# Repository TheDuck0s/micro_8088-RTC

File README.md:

# Micro 8088 + RTC

This is an IBM XT-compatible CPU and RTC card, based on a design by [Sergey Kiselev](https://github.com/skiselev) and [Aitor Gómez García](https://github.com/spark2k06).

# The Idea

The goal of this project is to create an XT-compatible computer on a passive backplane with a modular card-based architecture, minimizing the overall footprint while providing support for all common expansion cards.

# Hardware Documentation
Schematic PDF:
[Schematic - Version 1.0](Micro_8088-RTC_Schematic.pdf)

PCB PDF:
[Board Design - Version 1.0](Micro_8088-RTC_Board_Design.pdf)

Gerber Files:
[Gerber- Version 1.0](gerber/)

SPLD:

* U16 CPU-Part:
[Use the repository provided by Sergey Kiselev](https://github.com/skiselev/micro_8088/tree/master/SPLD)

* U17 RTC-Part:
[Use the repository provided by Sergey Kiselev](https://github.com/skiselev/RTC8088/tree/main/SPLD)

AT2XT Firmware:
* U15 [minuszerodegrees.net](http://minuszerodegrees.net/at2xtkb/XTATKEY_094.zip)

# Bill of Materials

Component type    	| Reference | Description                       | Quantity 
------------------ | --------- | --------------------------------- | -------- 
PCB                |           | Micro 8080 + RTC PCB              | 1        
Integrated Circuit | U1        | Intel 8088, 80C88, or NEC V20 CPU | 1        
Integrated Circuit | U2        | Intel 8087 FPU                    | 1        
Integrated Circuit | U3        | Faraday FE2010A                   | 1        
Integrated Circuit | U4        | SST39SF010A Flash ROM, DIP-32 package | 1    
Integrated Circuit | U5, U6    | AS6C4008 SRAM, DIP-32 package     | 2        
Integrated Circuit | U7 - U9   | 74F573 Octal D-Type Latch         | 3        
Integrated Circuit | U10, U11  | 74F245 Octal Bus Transceiver      | 2        
Integrated Circuit | U12, U13  | 74F244 Octal Buffer               | 2        
Integrated Circuit | U14       | 74F00 Quad 2-Input NAND Gate      | 1        
Integrated Circuit | U15       | PIC12F629 Microcontroller         | 1        
Integrated Circuit | U16       | ATF16V8B SPLD                     | 1        
IC Socket          | U1, U2    | DIP-40, 600 mil socket            | 2        
IC Socket          | U3        | PLCC-84 through hole socket       | 1        
IC Socket          | U4-U6     | DIP-32, 600 mil socket            | 3        
IC Socket          | U7-U13, U16, U17 | DIP-20, 300 mil socket     | 9        
IC Socket          | U14       | DIP-14, 300 mil socket            | 1        
IC Socket          | U15       | DIP-8, 300 mil socket             | 1        
IC Socket          | U18       | DIP-24, 600 mil socket            | 1
Diode              | D1        | 1N4148                            | 1        
LED                | D2        | 3 mm, green LED indicator         | 1        
Transistor         | Q1        | PN2222A, 2.54mm lead spacing      | 1        
Crystal            | X1        | 28.63636 MHz, 18 pF, HC-49/S      | 1        
Crystal            | X2        | 32768Hz                           | 1
Battery            | BT1       | Battery socket                    | 1
Speaker            | SP1       | 12 mm speaker                     | 1        
Tactile Button     | SW1       | 6 mm tactile button, right angle  | 1        
DIP Switch         | SW2, SW3  | 3 positions                       | 2        
DIP Switch         | SW4       | 5 positions                       | 1        
Connector          | P1        | 6 pin Mini DIN, purple            | 1        
Pin Header         | P2        | 4 pin header, 2.54 mm pitch       | 1        
Pin Header         | P3, JP1-JP5 | 2 pin header, 2.54 mm pitch     | 6        
Capacitor          | C1 - C18  | 0.1 uF, MLCC, 5 mm lead spacing   | 19       
Capacitor          | C18 - C20 | 10 uF, MLCC, 5 mm lead spacing    | 3        
Trimmer Capacitor  | C21       | 6.5-30 pF, 5 mm lead spacing      | 1        
Capacitor          | C22       | 47 pF, MLCC, 5 mm lead spacing    | 1        
Capacitor          | C23       | 0.01 uF, MLCC, 5 mm lead spacing  | 1        
Resistor Array     | RR1       | 4.7 k, bussed, 10 pin SIP         | 1        
Resistor Array     | RR2       | 10 k, bussed, 10 pin SIP          | 1        
Resistor Array     | RR3, RR4  | 4.7 k, bussed, 6 pin SIP          | 2        
Resistor Array     | RR5, RR6  | 10 k, bussed, 6 pin SIP           | 2        
Resistor           | R1        | 33 ohm, through hole              | 1        
Resistor           | R2, R3    | 47 ohm, through hole              | 2        
Resistor           | R4, R5    | 470 ohm, through hole             | 2        
Resistor           | R6        | 1 kohm, through hole              | 1        
Resistor           | R7        | 10 kohm, through hole             | 1        
Resistor           | R8        | 1 Mohm, through hole              | 1        
Fuse               | F1        | 1.1A polyfuse, 5.08 mm lead pitch | 1        
ISA Bracket        |           | Keystone Electronics 9202         | 1        
Screw              |           | 4-40 x 1/4" Screw                 | 2        

# Release Notes

### Changes:

#### Version 1.0

 * Initial Release

# Benchmarks
 * CPU: D70108HCZ-16
 * FPU: 8087-1

### Checkit 3.0 Benchmark:
#### @4.77 MHz
 * 414 Dhrystones (1.20x)
 * 126.9K Whetstones (19.23x)

#### @7.16 MHz
 * 618 Dhrystones (1.80x)
 * 191.3K Whetstones (28.97x)

#### @9.55 MHz
 * 837 Dhrystones (2.43x)
 * 267.7K Whetstones (40.56x)

# Final Note
 * Install either U14 or U16, not both together
 * The card is tested and works.
 * This card won't fit Sergey's case ([this one](https://github.com/skiselev/micro_8088_case)). The case will need to be enlarged.
 * Card size 185.3 mm x 102.9 mm

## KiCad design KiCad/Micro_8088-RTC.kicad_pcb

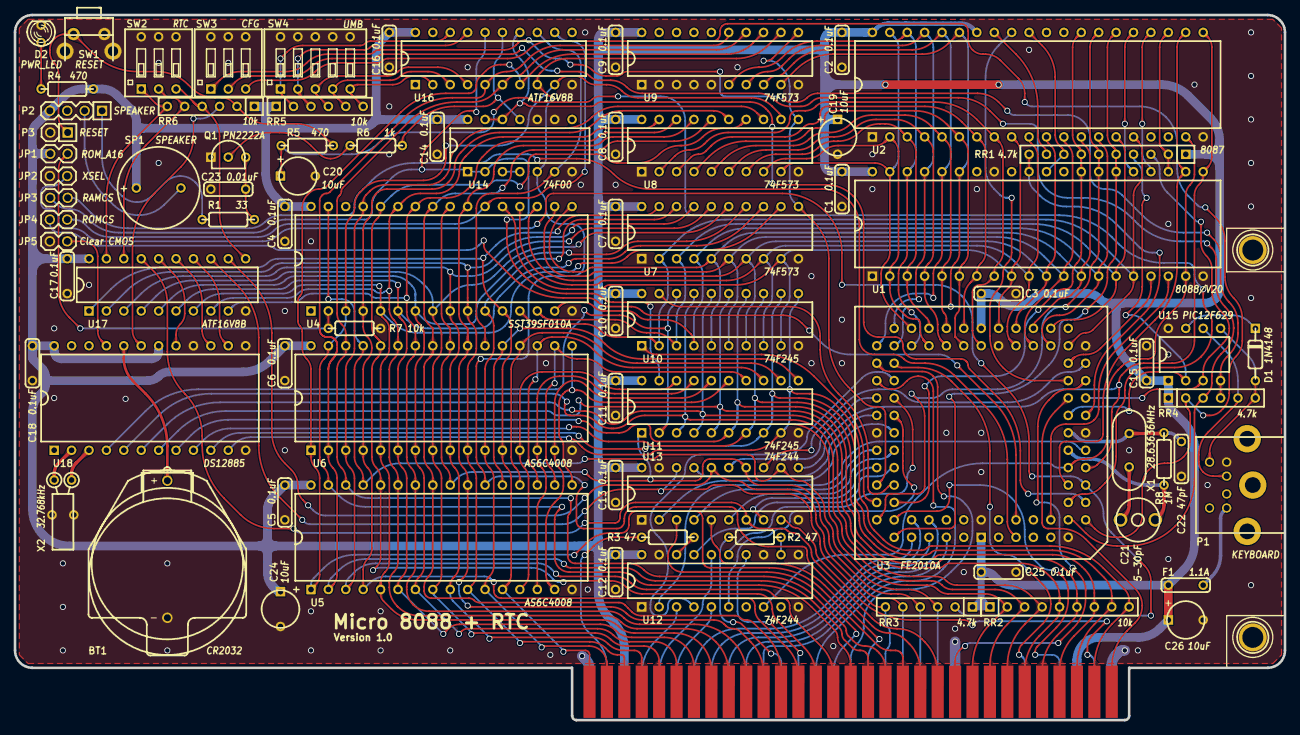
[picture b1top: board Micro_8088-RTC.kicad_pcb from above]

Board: 2 copper layers, 185.3 x 102.9 mm, 81 parts (0 on the bottom side), 160 nets.

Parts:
BT1: CR2032; Battery_Holder_CR2032_Universal
BUS1: BUSPC_HOST; Conn_Edge_PCB_ISA8
C1, C2, C3, C4, C5, C6, C7, C8, C9, C10, C11, C12, C13, C14, C15, C16, C17, C18, C25: 0.1uF; Cap_Cer_508
C19, C20, C24, C26: 10uF; Cap_Tant_508
C21: 5-30pF; C_Trim_Murata
C22: 47pF; Cap_Cer_508
C23: 0.01uF; Cap_Cer_508
D1: 1N4148; Diode_762
D2: PWR_LED; LED_3mm
F1: 1.1A; Cap_Cer_508
HOLE1, HOLE2: HOLE; Hole_3mm
JP1: ROM_A16; Conn_Pin_Header_2x1_2.54mm_NoKey
JP2: XSEL; Conn_Pin_Header_2x1_2.54mm_NoKey
JP3: RAMCS; Conn_Pin_Header_2x1_2.54mm_NoKey
JP4: ROMCS; Conn_Pin_Header_2x1_2.54mm_NoKey
JP5: Clear CMOS; Conn_Pin_Header_2x1_2.54mm_NoKey
P1: KEYBOARD; Conn_Mini_DIN_6pin
P2: SPEAKER; Conn_Pin_Header_4x1_2.54mm
P3: RESET; Conn_Pin_Header_2x1_2.54mm
Q1: PN2222A; Transistor_TO92_EBC_254
R1: 33; Res_762
R2, R3: 47; Res_762
R4, R5: 470; Res_762
R6: 1k; Res_762
R7: 10k; Res_762
R8: 1M; Res_762
RR1: 4.7k; Conn_SIL10
RR2: 10k; Conn_SIL9
RR3, RR4: 4.7k; Conn_SIL6
RR5, RR6: 10k; Conn_SIL6
SP1: SPEAKER; Speaker_12mm
SW1: RESET; Switch_Tactile_6mm_Right
SW2: RTC; Switch_DIP_3_Positions
SW3: CFG; Switch_DIP_3_Positions
SW4: UMB; Switch_DIP_5_Positions
U1: 8088/V20; IC_DIP40_600
U2: 8087; IC_DIP40_600
U3: FE2010A; IC_PLCC84_TH
U4: SST39SF010A; IC_DIP32_600
U5, U6: AS6C4008; IC_DIP32_600
U7, U8, U9: 74F573; IC_DIP20_300
U10, U11: 74F245; IC_DIP20_300
U12, U13: 74F244; IC_DIP20_300
U14: 74F00; IC_DIP14_300
U15: PIC12F629; IC_DIP8_300
U16, U17: ATF16V8B; IC_DIP20_300
U18: DS12885; IC_DIP24_600
X1: 28.63636MHz; Crystal_HC-49U_Vert
X2: 32.768kHz; Crystal_32K_Horiz

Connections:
/A0: BUS1.62 (SA0), U4.12 (A0), U5.12 (A0), U6.12 (A0), U7.19 (O0), U17.1 (I/CLK)
/A1: BUS1.61 (SA1), U4.11 (A1), U5.11 (A1), U6.11 (A1), U7.18 (O1)
/A2: BUS1.60 (SA2), U4.10 (A2), U5.10 (A2), U6.10 (A2), U7.17 (O2), U17.2 (I1)
/A3: BUS1.59 (SA3), U4.9 (A3), U5.9 (A3), U6.9 (A3), U7.16 (O3), U17.3 (I2)
/A4: BUS1.58 (SA4), U4.8 (A4), U5.8 (A4), U6.8 (A4), U7.15 (O4), U17.4 (I3)
/A5: BUS1.57 (SA5), U4.7 (A5), U5.7 (A5), U6.7 (A5), U7.14 (O5), U17.5 (I4)
/A6: BUS1.56 (SA6), U4.6 (A6), U5.6 (A6), U6.6 (A6), U7.13 (O6), U17.6 (I5)
/A7: BUS1.55 (SA7), U4.5 (A7), U5.5 (A7), U6.5 (A7), U7.12 (O7), U17.7 (I6)
/A8: BUS1.54 (SA8), U4.27 (A8), U5.27 (A8), U6.27 (A8), U8.19 (O0), U17.8 (I7)
/A9: BUS1.53 (SA9), U4.26 (A9), U5.26 (A9), U6.26 (A9), U8.18 (O1), U17.9 (I8)
/A10: BUS1.52 (SA10), U4.23 (A10), U5.23 (A10), U6.23 (A10), U8.17 (O2)
/A11: BUS1.51 (SA11), U4.25 (A11), U5.25 (A11), U6.25 (A11), U8.16 (O3)
/A12: BUS1.50 (SA12), U4.4 (A12), U5.4 (A12), U6.4 (A12), U8.15 (O4)
/A13: BUS1.49 (SA13), U4.28 (A13), U5.28 (A13), U6.28 (A13), U8.14 (O5)
/A14: BUS1.48 (SA14), U4.29 (A14), U5.3 (A14), U6.3 (A14), U8.13 (O6)
/A15: BUS1.47 (SA15), U4.3 (A15), U5.31 (A15), U6.31 (A15), U8.12 (O7), U16.9 (I8)
/A16: BUS1.46 (SA16), U5.2 (A16), U6.2 (A16), U9.15 (O4), U16.5 (I4)
/A17: BUS1.45 (SA17), U5.30 (A17), U6.30 (A17), U9.14 (O5), U16.6 (I5)
/A18: BUS1.44 (SA18), U5.1 (A18), U6.1 (A18), U9.13 (O6), U16.7 (I6)
/A19: BUS1.43 (SA19), U5.22 (~CE), U9.12 (O7), U14.5, U16.8 (I7)
/AA8: U1.8 (A8), U2.8 (AD8), U3.44 (A8), U8.2 (D0)
/AA9: U1.7 (A9), U2.7 (AD9), U3.45 (A9), U8.3 (D1)
/AA10: U1.6 (A10), U2.6 (AD10), U3.46 (A10), U8.4 (D2)
/AA11: U1.5 (A11), U2.5 (AD11), U3.47 (A11), U8.5 (D3)
/AA12: U1.4 (A12), U2.4 (AD12), U3.48 (A12), U8.6 (D4)
/AA13: U1.3 (A13), U2.3 (AD13), U3.49 (A13), U8.7 (D5)
/AA14: U1.2 (A14), U2.2 (AD14), U3.50 (A14), U8.8 (D6)
/AA15: U1.39 (A15), U2.39 (AD15), U3.51 (A15), U8.9 (D7)
/AA16: U1.38 (A16/S3), U2.38 (A16/S3), U3.52 (A16), U9.6 (D4)
/AA17: U1.37 (A17/S4), U2.37 (A17/S4), U3.53 (A17), U9.7 (D5)
/AA18: U1.36 (A18/S5), U2.36 (A18/S5), U3.54 (A18), U9.8 (D6)
/AA19: U1.35 (A19/S6), U2.35 (A19/S6), U3.55 (A19), U9.9 (D7)
/AD0: U1.16 (AD0), U2.16 (AD0), U3.34 (AD0), U4.13 (DQ0), U7.2 (D0), U10.2 (A1)
/AD1: U1.15 (AD1), U2.15 (AD1), U3.35 (AD1), U4.14 (DQ1), U7.3 (D1), U10.3 (A2)
/AD2: U1.14 (AD2), U2.14 (AD2), U3.36 (AD2), U4.15 (DQ2), U7.4 (D2), U10.4 (A3)
/AD3: U1.13 (AD3), U2.13 (AD3), U3.37 (AD3), U4.17 (DQ3), U7.5 (D3), U10.5 (A4)
/AD4: U1.12 (AD4), U2.12 (AD4), U3.38 (AD4), U4.18 (DQ4), U7.6 (D4), U10.6 (A5)
/AD5: U1.11 (AD5), U2.11 (AD5), U3.39 (AD5), U4.19 (DQ5), U7.7 (D5), U10.7 (A6)
/AD6: U1.10 (AD6), U2.10 (AD6), U3.40 (AD6), U4.20 (DQ6), U7.8 (D6), U10.8 (A7)
/AD7: U1.9 (AD7), U2.9 (AD7), U3.41 (AD7), U4.21 (DQ7), U7.9 (D7), U10.9 (A8)
/AEN: BUS1.42 (AEN), U13.7 (Y2), U17.17 (I/O3)
/ALE: BUS1.28 (ALE), U12.3 (Y4)
/APNMI: U2.32 (INT), U3.29 (APNMI)
/AS0: RR6.6, SW2.1, U17.19 (I/O1)
/AS1: RR6.5, SW2.2, U17.18 (I/O2)
/AS2: RR6.4, SW2.3, U17.11 (I9/~OE)
/AT_KBCLK: D1.2 (A), P1.5, RR4.6, U15.5 (GP2/T0CKI/INT/COUT)
/AT_KBDATA: P1.1, RR4.5, U15.6 (GP1/CIN-/ICSPCLK)
/CLK: BUS1.20 (CLK), R2.1
/CLK88: U1.19 (CLK), U2.19 (CLK), U3.19 (CLOCK), U12.8 (A4)
/D0: BUS1.40 (SD0), RR2.2, U10.18 (B1), U11.2 (A1), U18.4 (AD0)
/D1: BUS1.39 (SD1), RR2.3, U10.17 (B2), U11.3 (A2), U18.5 (AD1)
/D2: BUS1.38 (SD2), RR2.4, U10.16 (B3), U11.4 (A3), U18.6 (AD2)
/D3: BUS1.37 (SD3), RR2.5, U10.15 (B4), U11.5 (A4), U18.7 (AD3)
/D4: BUS1.36 (SD4), RR2.6, U10.14 (B5), U11.6 (A5), U18.8 (AD4)
/D5: BUS1.35 (SD5), RR2.7, U10.13 (B6), U11.7 (A6), U18.9 (AD5)
/D6: BUS1.34 (SD6), RR2.8, U10.12 (B7), U11.8 (A7), U18.10 (AD6)
/D7: BUS1.33 (SD7), RR2.9, U10.11 (B8), U11.9 (A8), U18.11 (AD7)
/DRQ1: BUS1.18 (DRQ1), U3.58 (DRQ1)
/DRQ2: BUS1.6 (DRQ2), U3.57 (DRQ2)
/DRQ3: BUS1.16 (DRQ3), U3.56 (DRQ3)
/DTR: U3.72 (DTR), U10.1 (DIR)
/E0_PASS: RR4.4, SW3.1, U15.4 (GP3/~MCLR/Vpp)
/EOP: U3.59 (EOP), U12.4 (A2)
/INT: U1.18 (INTR), U3.10 (INT)
/IORDY: BUS1.41 (IO_READY), U3.28 (IORDY)
/IRQ2: BUS1.4 (IRQ2), U3.76 (IRQ2)
/IRQ3: BUS1.25 (IRQ3), U3.77 (IRQ3)
/IRQ4: BUS1.24 (IRQ4), U3.78 (IRQ4)
/IRQ5: BUS1.23 (IRQ5), U3.79 (IRQ5)
/IRQ6: BUS1.22 (IRQ6), U3.80 (IRQ6)
/IRQ7: BUS1.21 (IRQ7), U3.81 (IRQ7)
/KBCLK: RR1.4, U3.25 (KBCLK), U15.2 (GP5/T1CKI/OSC1/CLKIN)
/KBDATA: RR1.3, U3.26 (KBDA), U15.3 (GP4/~T1G/OSC2/CLKOUT)
/KBD_VCC: F1.1, P1.4
/LE: U3.70 (ALE), U7.11 (LE), U8.11 (LE), U9.11 (LE)
/MD0: U5.13 (DQ0), U6.13 (DQ0), U11.18 (B1)
/MD1: U5.14 (DQ1), U6.14 (DQ1), U11.17 (B2)
/MD2: U5.15 (DQ2), U6.15 (DQ2), U11.16 (B3)
/MD3: U5.17 (DQ3), U6.17 (DQ3), U11.15 (B4)
/MD4: U5.18 (DQ4), U6.18 (DQ4), U11.14 (B5)
/MD5: U5.19 (DQ5), U6.19 (DQ5), U11.13 (B6)
/MD6: U5.20 (DQ6), U6.20 (DQ6), U11.12 (B7)
/MD7: U5.21 (DQ7), U6.21 (DQ7), U11.11 (B8)
/NMI: U1.17 (NMI), U3.31 (NMI)
/OSC: U3.20 (OSC), U12.2 (A1)
/OSCDRV: BUS1.30 (OSC), R3.1
/QS0: U1.25 (QS0), U2.25 (QS0)
/QS1: U1.24 (QS1), U2.24 (QS1)
/READY: U1.22 (READY), U2.22 (READY), U3.17 (READY)
/RESET: U1.21 (RESET), U2.21 (RESET), U3.18 (RESET), U13.11 (A1)
/ROM_A16: JP1.1, R7.2, U4.2 (A16)
/RSTDRV: BUS1.2 (RESET), U13.9 (Y1)
/RTCALE: U17.14 (I/O6), U18.14 (AS)
/RTCRD: U17.16 (I/O4), U18.17 (DS)
/RTCWR: U17.15 (I/O5), U18.15 (R/~W)
/SPKR: U3.14 (SPEAKR), U14.12, U14.13, U16.14 (I/O6)
/TC: BUS1.27 (TC), U12.16 (Y2)
/XAEN: U3.30 (AEN), U13.13 (A2)
/XALE: U3.69 (BALE), U12.17 (A4)
/XSEL: JP2.2, RR3.2, U3.16 (XSEL)
/~DACK0: BUS1.19 (DACK0), U12.14 (Y3)
/~DACK1: BUS1.17 (DACK1), U13.3 (Y4)
/~DACK2: BUS1.26 (DACK2), U12.5 (Y3)
/~DACK3: BUS1.15 (DACK3), U13.5 (Y3)
/~DEN: U3.71 (~DEN), U10.19 (~G)
/~EPSL: JP4.1, U3.6 (~EPSL)
/~IOCHK: BUS1.32 (IO_CH_CK), U3.27 (~IOCHK)
/~IOR: BUS1.14 (IOR), RR3.6, U13.18 (Y1), U17.13 (I/O7)
/~IOW: BUS1.13 (IOW), RR3.5, U13.16 (Y2), U17.12 (I/O8)
/~IRQ: RR6.3, U18.19 (~IRQ)
/~MEMR: BUS1.12 (MEMR), RR3.4, U4.24 (~OE), U5.24 (~OE), U6.24 (~OE), U11.1 (DIR), U13.14 (Y3)
/~MEMW: BUS1.11 (MEMW), RR3.3, U4.31 (~WE), U5.29 (~WE), U6.29 (~WE), U13.12 (Y4)
/~RAMCS2: U6.22 (~CE), U14.6, U16.13 (I/O7)
/~RAMCS: JP3.1, U3.5 (~RAMCS)
/~RAMENA: JP3.2, U11.19 (~G), U14.1, U14.2, U16.16 (I/O4)
/~RESIN: P3.1, R5.2, RR6.2, SW1.2
/~ROMCS: JP4.2, U4.22 (~CE), U16.12 (I/O8)
/~RQ/GT0: RR1.10, U1.31 (~RQ/~GT0), U3.24 (~RQ/GT)
/~RQ/GT1: RR1.8, U1.30 (~RQ/~GT1), U2.31 (~RQ/~GT0)
/~RQ/GT2: RR1.9, U2.33 (~RQ/~GT1)
/~S0: RR1.5, U1.26 (~S0), U2.26 (~S0), U3.75 (~S0)
/~S1: RR1.6, U1.27 (~S1), U2.27 (~S1), U3.74 (~S1)
/~S2: RR1.7, U1.28 (~S2), U2.28 (~S2), U3.73 (~S2)
/~SPKR: R6.2, U14.11, U16.15 (I/O5)
/~TEST: RR1.2, U1.23 (~TEST), U2.23 (BUSY)
/~VID0: RR4.2, SW3.3, U3.12 (VID0)
/~VID1: RR4.3, SW3.2, U3.13 (VID1)
/~XDACK0: U3.63 (~DACK0), U12.6 (A3)
/~XDACK1: U3.62 (~DACK1), U13.17 (A4)
/~XDACK2: U3.61 (~DACK2), U12.15 (A3)
/~XDACK3: U3.60 (~DACK3), U13.15 (A3)
/~XIOR: U3.65 (~IOR), U13.2 (A1)
/~XIOW: U3.66 (~IOW), U13.4 (A2)
/~XMEMR: U3.67 (~MEMR), U13.6 (A3)
/~XMEMW: U3.68 (~MEMW), U13.8 (A4)
GND: BT1.2 (-), BUS1.1 (GND), BUS1.10 (GND), BUS1.31 (GND), C1.2, C2.2, C3.2, C4.2, C5.2, C6.2, C7.2, C8.2, C9.2, C10.2, C11.2, C12.2, C13.2, C14.2, C15.2, C16.2, C17.2, C18.2, C19.2, C20.2, C22.2, C23.2, C24.2, C25.2, C26.2, D2.1 (K), HOLE1.1, HOLE2.1, JP2.1, JP5.2 (B), P1.3, P3.2, Q1.1 (E), R7.1, SW1.1, SW1.GND, SW2.4, SW2.5, SW2.6, SW3.4, SW3.5, SW3.6, SW4.6, SW4.7, SW4.8, SW4.9, SW4.10, U1.1 (GND), U1.20 (GND), U1.33 (~MX), U2.1 (GND), U2.20 (GND), U3.2 (GND), U3.11 (A64K), U3.22 (GND), U3.32 (PTYIN), U3.42 (GND), U3.64 (GND), U4.16 (GND), U5.16 (GND), U6.16 (GND), U7.1 (~OE), U7.10 (GND), U8.1 (~OE), U8.10 (GND), U9.1 (~OE), U9.2 (D0), U9.3 (D1), U9.4 (D2), U9.5 (D3), U9.10 (GND), U10.10 (GND), U11.10 (GND), U12.1 (~G), U12.10 (GND), U12.11 (A1), U12.13 (A2), U12.19 (~G), U13.1 (~G), U13.10 (GND), U13.19 (~G), U14.7 (GND), U14.9, U14.10, U15.8 (GND), U16.10 (GND), U17.10 (GND), U18.12 (GND), U18.13 (~CS), U18.16 (GND), X2.3
unnamed: BT1.1 (+), U18.20 (VBAT)
unnamed: C21.1, X1.1
unnamed: D1.1 (K), U15.7 (GP0/CIN+/ISCPDAT)
unnamed: D2.2 (A), R4.2
unnamed: JP5.1 (A), U18.21 (~RCLR)
unnamed: P2.1, R1.1
unnamed: P2.2, SP1.1
unnamed: Q1.2 (B), R6.1
unnamed: C23.1, Q1.3 (C), R1.2
unnamed: C22.1, R8.1, U3.23 (X1), X1.2
unnamed: C21.2, R8.2, U3.21 (X2)
unnamed: C20.1, R5.1, U3.15 (~REST)
unnamed: R3.2, U12.18 (Y1)
unnamed: R2.2, U12.12 (Y4)
unnamed: U14.3, U14.4
unnamed: RR5.6, SW4.5, U16.2 (I1)
unnamed: RR5.5, SW4.4, U16.3 (I2)
unnamed: RR5.4, SW4.3, U16.4 (I3)
unnamed: RR5.2, SW4.1, U16.18 (I/O2)
unnamed: RR5.3, SW4.2, U16.17 (I/O3)
unnamed: U18.2 (X1), X2.1
unnamed: U18.3 (X2), X2.2
VCC: BUS1.3 (VCC), BUS1.29 (VCC), C1.1, C2.1, C3.1, C4.1, C5.1, C6.1, C7.1, C8.1, C9.1, C10.1, C11.1, C12.1, C13.1, C14.1, C15.1, C16.1, C17.1, C18.1, C19.1, C24.1, C25.1, C26.1, F1.2, JP1.2, P2.4, R4.1, RR1.1 (COM), RR2.1 (COM), RR3.1 (COM), RR4.1 (COM), RR5.1 (COM), RR6.1 (COM), SP1.2, U1.40 (VCC), U2.34 (~BHE/S7), U2.40 (VCC), U3.1 (VCC), U3.43 (VCC), U4.32 (VCC), U5.32 (VCC), U6.32 (VCC), U7.20 (VCC), U8.20 (VCC), U9.20 (VCC), U10.20 (VCC), U11.20 (VCC), U12.20 (VCC), U13.20 (VCC), U14.14 (VCC), U15.1 (VCC), U16.20 (VCC), U17.20 (VCC), U18.18 (~RESET), U18.24 (VCC)
